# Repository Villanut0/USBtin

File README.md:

# USBtin USB to CAN interface clone

USBtin is a simple USB to CAN interface. It can monitor CAN busses and transmit CAN messages. USBtin implements the USB CDC class and creates a virtual comport on the host computer.

**This PCB is a clone of the original project :** [USBtin](https://www.fischl.de/usbtin/)

It is almost the same as the original PCB. I made it to be able to mill it easily on my cheap milling machine.

## Features
* 65x32mm
* Single sided PCB with only 2 straps
* Same through-hole components as the original project ([Partlist](https://www.fischl.de/usbtin/#partlist))
* [Interactive BOM](http://htmlpreview.github.io/?https://github.com/Villanut0/USBtin/blob/master/bom/ibom.html)

## Screenshots

## Enclosure
3D printed enclosure is available on [Thingiverse](https://www.thingiverse.com/thing:3976971)

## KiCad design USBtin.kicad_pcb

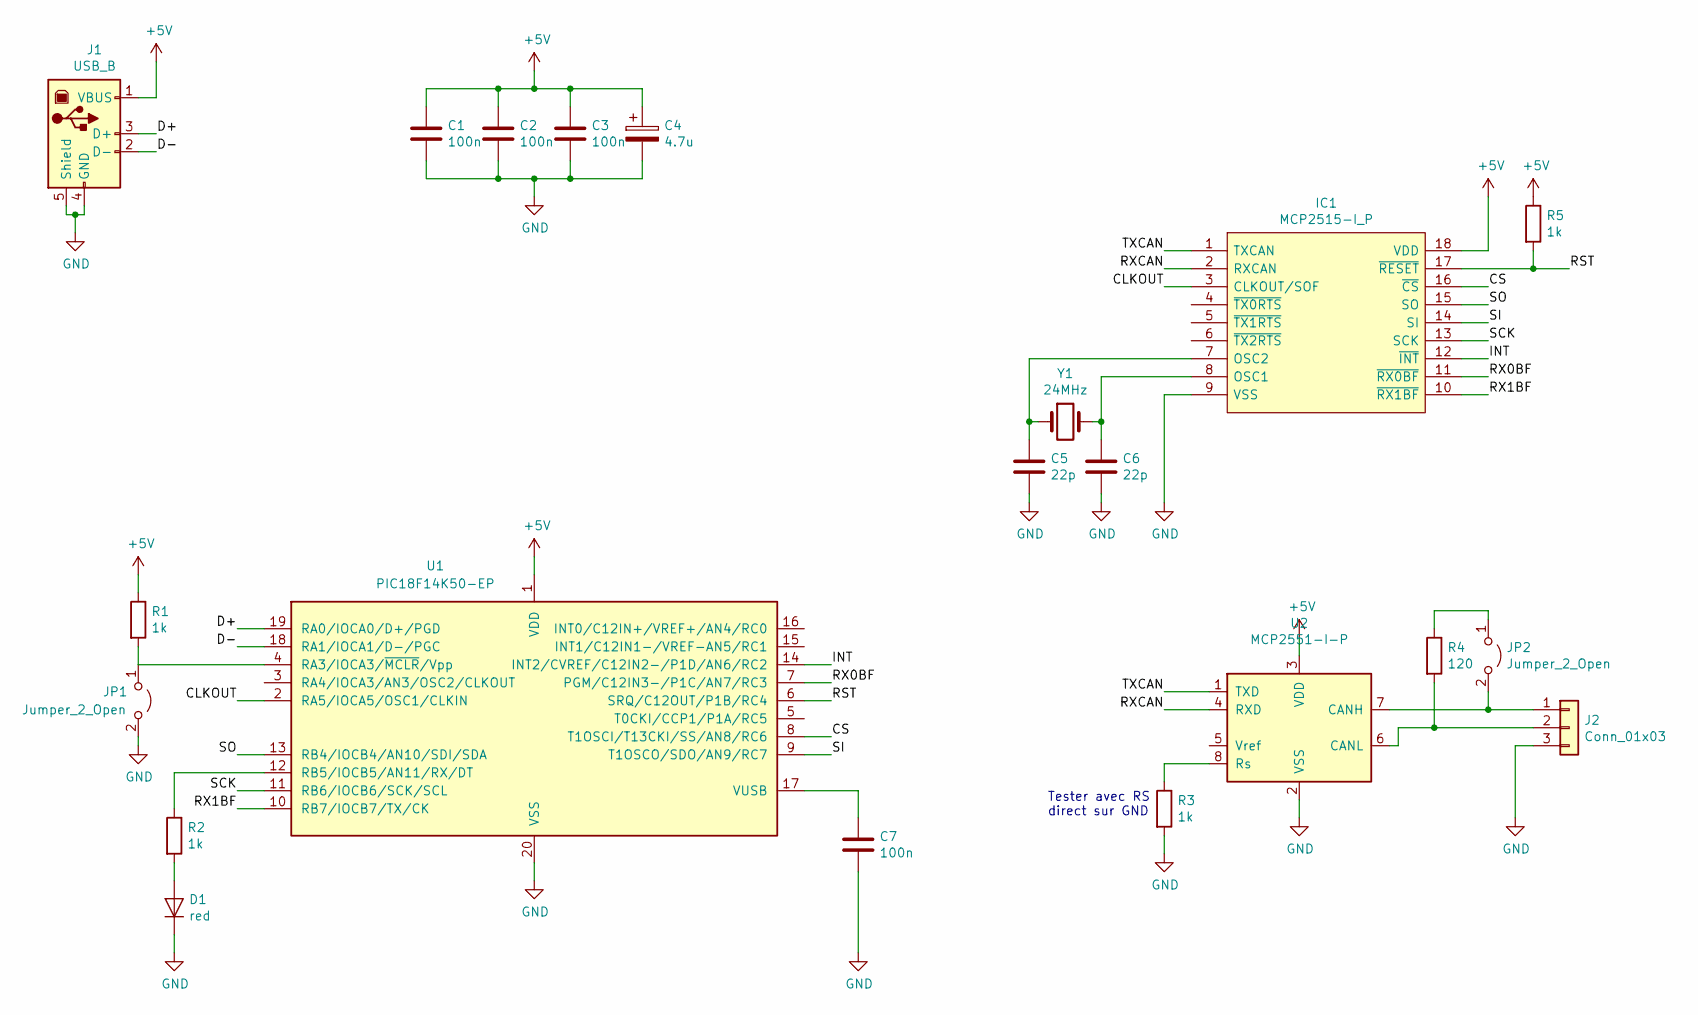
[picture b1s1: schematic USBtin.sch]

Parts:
C1, C2, C3, C7: 100n; C_Disc_D5.1mm_W3.2mm_P5.00mm
C4: 4.7u; CP_Radial_D5.0mm_P2.50mm
C5, C6: 22p; C_Disc_D3.4mm_W2.1mm_P2.50mm
D1: red; LED_D3.0mm
IC1: MCP2515-I_P; DIP-18_W7.62mm; Manufacturer_Part_Number MCP2515-I/P; Mouser Part Number 579-MCP2515-I/P
J1: USB_B; USB_B_OST_USB-B1HSxx_Horizontal
J2: Conn_01x03; TerminalBlock_RND_205-00002_1x03_P5.00mm_Horizontal
JP1, JP2: Jumper_2_Open; PinHeader_1x02_P2.54mm_Vertical
R1, R2, R3, R5: 1k; R_Axial_DIN0411_L9.9mm_D3.6mm_P5.08mm_Vertical
R4: 120; R_Axial_DIN0411_L9.9mm_D3.6mm_P5.08mm_Vertical
U1: PIC18F14K50-EP; DIP-20_W7.62mm
U2: MCP2551-I-P; DIP-8_W7.62mm
Y1: 24MHz; Crystal_HC49-U_Vertical

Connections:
+5V: C1.1, C2.1, C3.1, C4.1, IC1.18 (VDD), J1.1 (VBUS), R1.1, R5.1, U1.1 (VDD), U2.3 (VDD)
/CLKOUT: IC1.3 (CLKOUT/SOF), U1.2 (RA5/IOCA5/OSC1/CLKIN)
/CS: IC1.16 (~CS), U1.8 (T1OSCI/T13CKI/SS/AN8/RC6)
/D+: J1.3 (D+), U1.19 (RA0/IOCA0/D+/PGD)
/D-: J1.2 (D-), U1.18 (RA1/IOCA1/D-/PGC)
/INT: IC1.12 (~INT), U1.14 (INT2/CVREF/C12IN2-/P1D/AN6/RC2)
/RST: IC1.17 (~RESET), R5.2, U1.6 (SRQ/C12OUT/P1B/RC4)
/RX0BF: IC1.11 (~RX0BF), U1.7 (PGM/C12IN3-/P1C/AN7/RC3)
/RX1BF: IC1.10 (~RX1BF), U1.10 (RB7/IOCB7/TX/CK)
/RXCAN: IC1.2 (RXCAN), U2.4 (RXD)
/SCK: IC1.13 (SCK), U1.11 (RB6/IOCB6/SCK/SCL)
/SI: IC1.14 (SI), U1.9 (T1OSCO/SDO/AN9/RC7)
/SO: IC1.15 (SO), U1.13 (RB4/IOCB4/AN10/SDI/SDA)
/TXCAN: IC1.1 (TXCAN), U2.1 (TXD)
GND: C1.2, C2.2, C3.2, C4.2, C5.2, C6.2, C7.2, D1.1 (K), IC1.9 (VSS), J1.4 (GND), J1.5 (Shield), J2.3, JP1.2 (B), R3.2, U1.20 (VSS), U2.2 (VSS)
unnamed: C5.1, IC1.7 (OSC2), Y1.1
unnamed: C6.1, IC1.8 (OSC1), Y1.2
unnamed: C7.1, U1.17 (VUSB)
unnamed: D1.2 (A), R2.2
unnamed: J2.1, JP2.2 (B), U2.7 (CANH)
unnamed: J2.2, R4.2, U2.6 (CANL)
unnamed: JP1.1 (A), R1.2, U1.4 (RA3/IOCA3/~MCLR~/Vpp)
unnamed: JP2.1 (A), R4.1
unnamed: R2.1, U1.12 (RB5/IOCB5/AN11/RX/DT)
unnamed: R3.1, U2.8 (Rs)

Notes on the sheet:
Tester avec RS direct sur GND

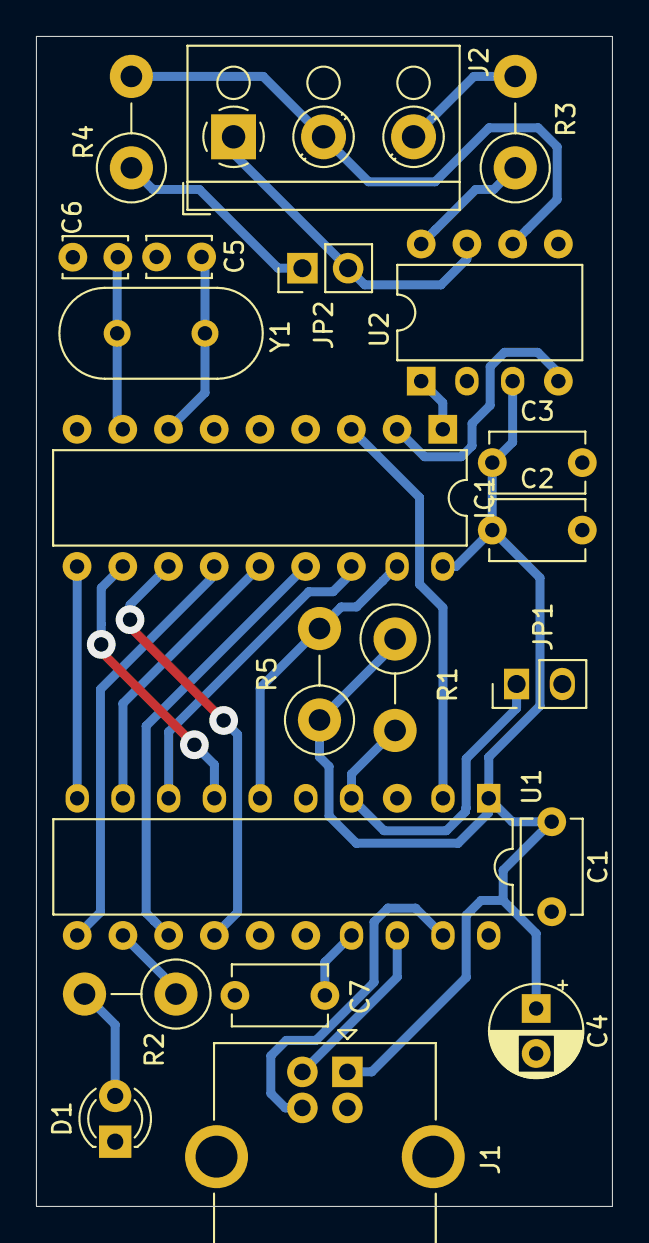
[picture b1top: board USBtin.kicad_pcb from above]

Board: 2 copper layers, 32.0 x 65.0 mm, 21 parts (0 on the bottom side), 25 nets.

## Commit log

2019-10-20 schematic and pcb done
2019-10-23 changing C4 to a polarize capacitor
2019-10-24 removing netlist
2019-10-24 adding origin
2019-10-25 rotate 90 degrees
2019-10-25 USB 3D model
2019-11-14 updated README, output files in gbr, schematic PDF
2019-11-14 adding lib cache
2019-11-16 removing comment on schematic
2020-01-15 Interactive BOM and update README
2020-01-15 Fix interactive BOM link
2020-01-16 .gitattributes and .gitignore
